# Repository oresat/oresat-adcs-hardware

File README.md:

# oresat-adcs-hardware

For more information on the OreSat project, please see <https://www.oresat.org/>!

## About this Repo

This repo contains the following projects:

* **The OreSat ADCS Card**
   * ADCS M0 microcontroller on its own OreSat Power Domain (OPD)
      * Power switch and LTC4300 that connects the M0 to:
         * BMI088 IMU (onboard the ADCS card)
         * LTC4305 2-Channel I2C Bus Multiplexer (one on each end cap via the backplane, end cards, and connectors to the end caps)
            * Two MMC5883MA magnetometers (two on each end cap, multiplexed by the LTC4305s)
      * Three STSPIN250s for the X, Y, and Z magnetorquers
   * Q1 Reaction Wheel OPD which powers the Q1 RW board
   * Q2 Reaction Wheel OPD which powers the Q2 RW board
   * Q3 Reaction Wheel OPD which powers the Q3 RW board
   * Q4 Reaction Wheel OPD which powers the Q4 RW board
* **OreSat RW boards**
   * Boards that run one of the four reaction wheels that we have.
   * Note that the "flat" version of the boards are for development

## LICENSE

Copyright the Portland State Aerospace Society, 2022.

This source describes Open Hardware that is licensed under CERN-OHL-S v2, or any later version.

You may redistribute and modify this source and make products using it under the terms of the CERN-OHL-S v2 (https://ohwr.org/cern_ohl_s_v2.txt).

This source is distributed WITHOUT ANY EXPRESS OR IMPLIED WARRANTY, INCLUDING OF MERCHANTABILITY, SATISFACTORY QUALITY AND FITNESS FOR A PARTICULAR PURPOSE. Please see the CERN-OHL-S v2 for applicable conditions.

Source location: https://github.com/oresat/

As per CERN-OHL-S v2 section 4, should You produce hardware based on this source, You must where practicable maintain the Source Location visible on the external case of the Gizmo or other products you make using this source.

# DEPRECATED - PLEASE EVENTUALLY REWRITE :)

## The OreSat Project
OreSat is an inter university collaboration to design an orbital vehicle. Once in orbit, the nanosatellite will engage in three missions. One of the missions is space testing a relatively new photovoltaic panel. The other missions require the ability to point at and maintain visual contact with a specified location. 
## Background Motivation   
In order to successfully complete these missions, OreSat will need to be able to articulate its orientation as well as its passive “drifting” spin (we’ll discuss what “passive spin” means a little later). 
Quick and reliable orientation adjustment and control will serve several purposes. It will allow the vehicle to direct its main camera, as well as giving it the ability to execute maneuvers that allow it to maintain visual and radio contact with a specific location. This makes taking photos and videos much easier, but it also allows us to have a segment of time to do large bandwidth data dumps to ground stations. This gives it the potential to do live video streaming. 
### Active Pointing
The method that was selected for active orientation on OreSat employs the use of internal spinning masses called reaction wheels. The basic principle is simple. If there is a free floating object and a section of it starts to spin, the rest of the body will react by spinning in the opposite direction. The spin rates are related, but not necessarily the same. If you’d like to look more into this, the concept is conservation of angular momentum. 
So the idea is that we have a pointing vector for Oresat (not poynting, that comes later), and an idea of the pointing vector to the location we would like to image. We simply take the difference, and then rotate the collective mass of all of the reaction wheels in the opposite direction until the satellite camera sees what we want it too.  
### Passive Spin Control
The term “passive spin” will be used to refer the net angular momentum of the nanosatellite. While the reaction wheels are active, they are able to control the direction and spin of the frame of the satellite, but only by effectively redistributing the momentum from the frame into the reaction wheel masses. The reaction wheels are incapable of altering the net angular momentum. The need for being able to modify the net momentum vector of the satellite helps alleviate the burden of two issues. The issues are thermal regulation and power generation. OreSat only has photovoltaic panels of its elongated faces. To maximize the amount of power, the desired passive spin of the satellite would put the long axis perpendicular to the sun. This maximizes the surface of exposure. There is another part to the total momentum though, and that is its magnitude. The rate of spin effects several things, but most notably it affects the temperature gradient experience by OreSat. If the satellite has no spin, then the side that the sun is hitting will heat continuously until OreSat passes behind the earth. This can cause several issues, most simply that having a hot spot would increase the likelihood of an electrical system to failing. Another issue is that the hot spot will cause different amounts of expansion in different areas of the frame, increasing the likelihood of failure. Another issue that hot spots cause is a drop in efficiency of the solar panels, making rotation partially an energy problem as well. 
Adding an intentional spin to OreSat will even out the thermal load applied to 

The attitude control system (ACS) inside oresat needs to orientate the position of the cubesat in space. This will be acheived in two ways; With brushless DC motors (BLDC) and with Magnetorquers. We are designing a PCB that controls both systems.

Find the project design contraints at,
[Project Design Constraints](https://github.com/oresat/oresat-acs-board/blob/master/Project%20Design%20Constraints.md)

ACS Level 2 Block Diagram Version 3.2

### System Hardware Overview
[Deatailed Hardware Reference Guide](https://github.com/oresat/oresat-acs-board/tree/master/Component%20File)

### EagleCAD Files:
[Link to the EagleCAD schematics and board layouts](https://github.com/oresat/oresat-acs-board/tree/master/eaglecad)

### Manufacturing Photos:
[Manufacturing photos of board layouts and CAD model of mounting strategy](https://github.com/oresat/oresat-acs-board/tree/master/Manufacturing%20photos)

### Capstone Poster:
[Link to Capstone poster in Google Drive](https://docs.google.com/presentation/d/1KBfbX376Y7nvsIXe14JdyOgP9TMmgJlgeOiYP8BOekc/edit#slide=id.p1)

### System Firmware:
[Check here for the firmware information](https://github.com/oresat/oresat-firmware/wiki/ACS-Firmware)

### Research and Tutorials / Ramp Up Documents:
Brushless DC (BLDC) motor control is a challenging form of motor control. We found numerous helpful tutorials and references.
[Link to research references and bibliography, start here for a ramp up on ACS](https://github.com/oresat/oresat-acs-board/blob/master/Ramp%20Up.md)

## Final Product:

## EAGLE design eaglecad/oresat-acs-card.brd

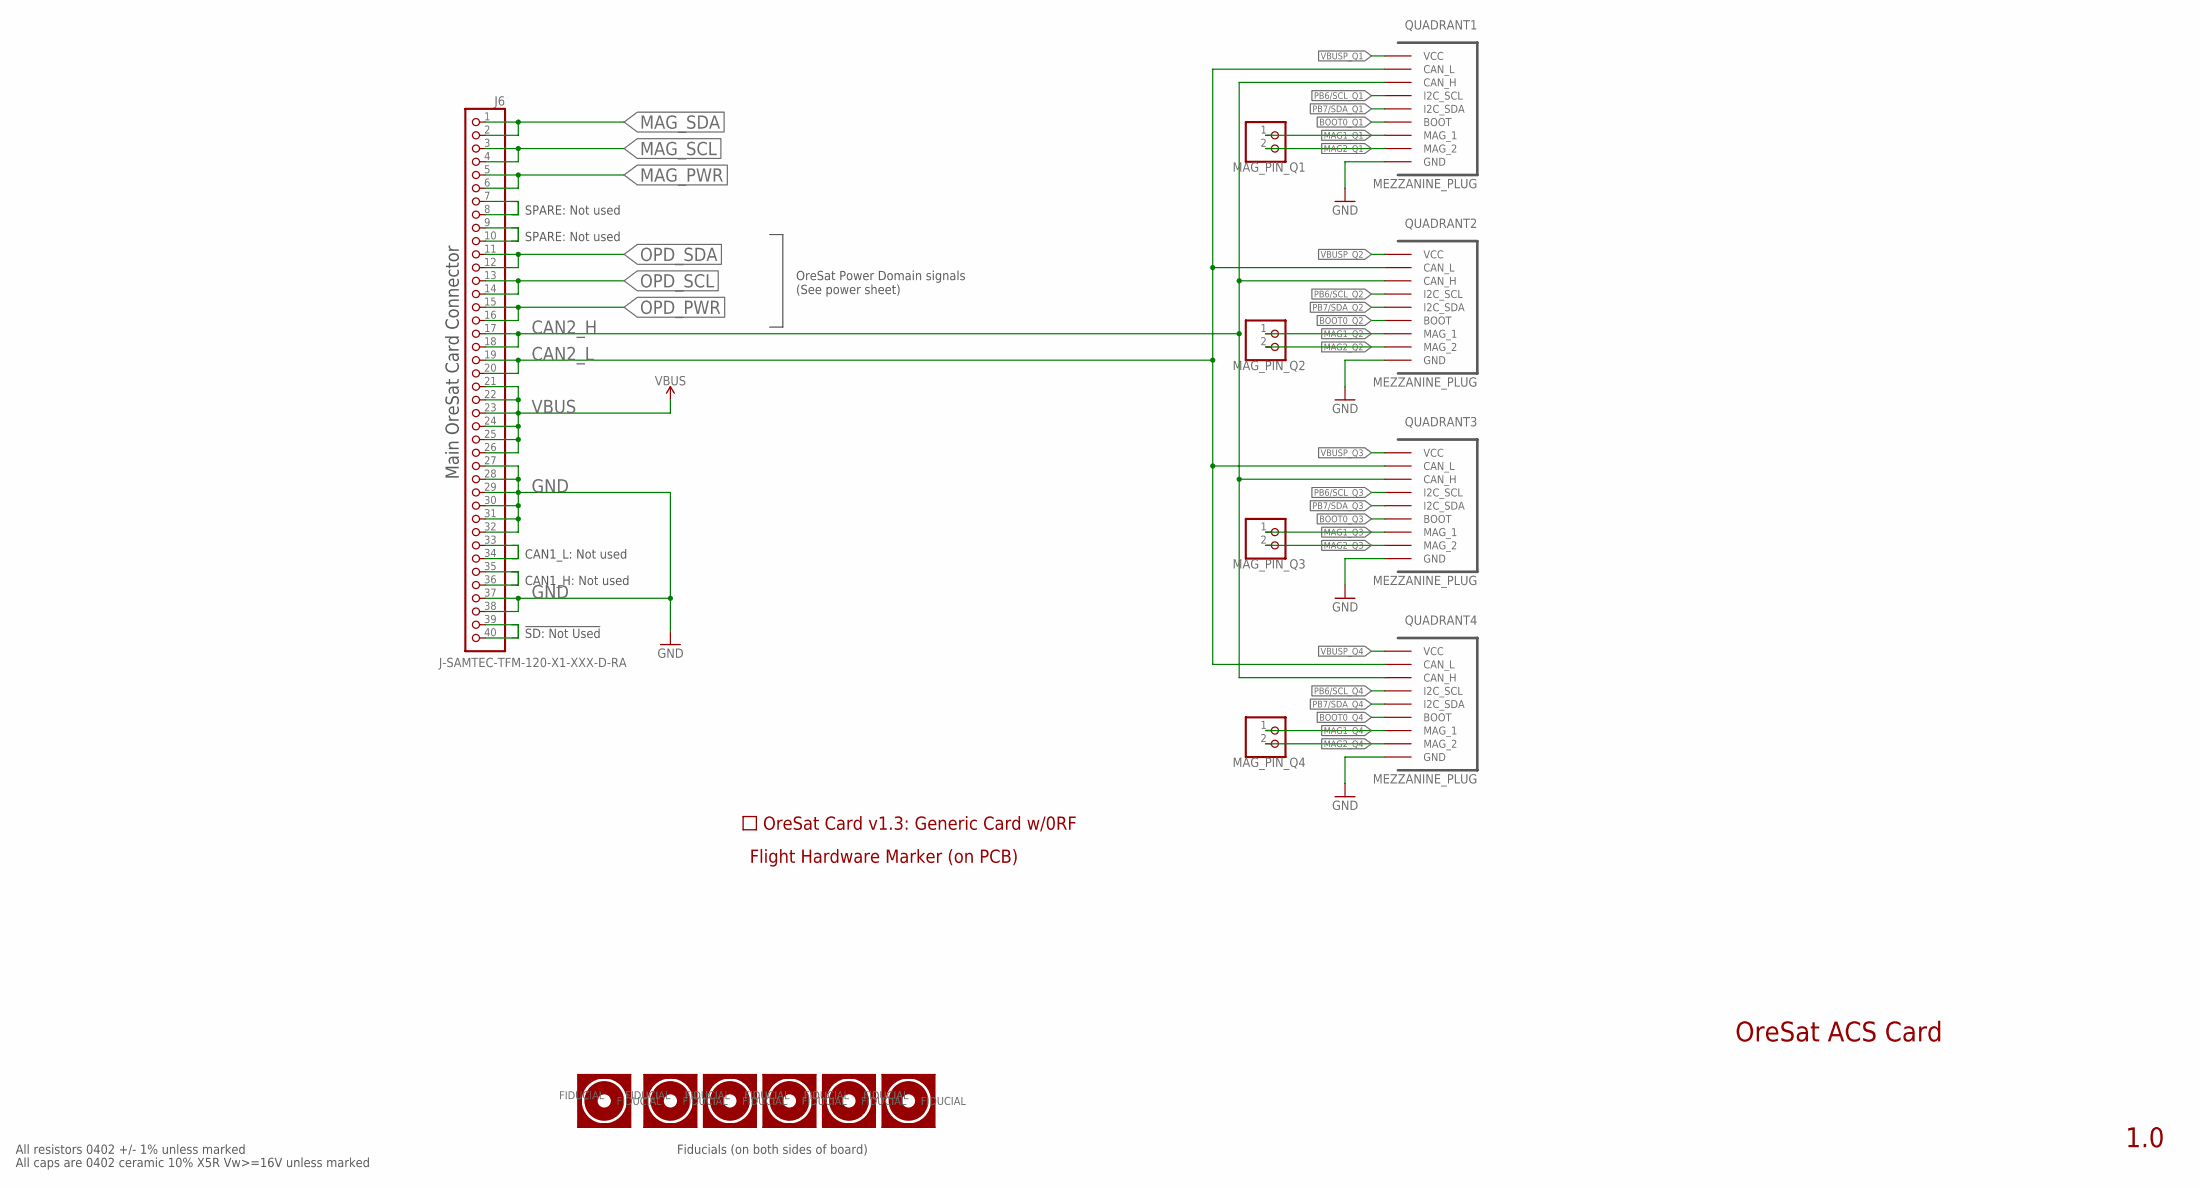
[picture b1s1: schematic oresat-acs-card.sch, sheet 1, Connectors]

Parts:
FIDUCIAL1, FIDUCIAL2, FIDUCIAL3, FIDUCIAL4, FIDUCIAL5, FIDUCIAL6: FIDUCIAL-1.0X2.0
J6: J-SAMTEC-TFM-120-X1-XXX-D-RA; MPN TFM-120-01-L-D-RA
MAG_PIN_Q1, MAG_PIN_Q2, MAG_PIN_Q3, MAG_PIN_Q4: PINHD-1X2; 1X02
PCB1: ORESAT-CARD-V1.3-GENERIC-0RF
QUADRANT1, QUADRANT2, QUADRANT3, QUADRANT4: MEZZANINE_PLUG; MPN 0555600307
U$1: FLIGHMARKERNEW; FLIGHTMARKER_NEW_BOARDS

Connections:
BOOT0_Q1: QUADRANT1.P$9 (BOOT), QUADRANT1.P$22 (BOOT); also elsewhere on the board
BOOT0_Q2: QUADRANT2.P$9 (BOOT), QUADRANT2.P$22 (BOOT); also elsewhere on the board
BOOT0_Q3: QUADRANT3.P$9 (BOOT), QUADRANT3.P$22 (BOOT); also elsewhere on the board
BOOT0_Q4: QUADRANT4.P$9 (BOOT), QUADRANT4.P$22 (BOOT); also elsewhere on the board
CAN2_H: J6.17, J6.18, QUADRANT1.P$6 (CAN_H), QUADRANT1.P$25 (CAN_H), QUADRANT2.P$6 (CAN_H), QUADRANT2.P$25 (CAN_H), QUADRANT3.P$6 (CAN_H), QUADRANT3.P$25 (CAN_H), QUADRANT4.P$6 (CAN_H), QUADRANT4.P$25 (CAN_H); also elsewhere on the board
CAN2_L: J6.19, J6.20, QUADRANT1.P$5 (CAN_L), QUADRANT1.P$26 (CAN_L), QUADRANT2.P$5 (CAN_L), QUADRANT2.P$26 (CAN_L), QUADRANT3.P$5 (CAN_L), QUADRANT3.P$26 (CAN_L), QUADRANT4.P$5 (CAN_L), QUADRANT4.P$26 (CAN_L); also elsewhere on the board
GND: J6.27, J6.28, J6.29, J6.30, J6.31, J6.32, J6.37, J6.38, QUADRANT1.P$1 (GND), QUADRANT1.P$2 (GND), QUADRANT1.P$14 (GND), QUADRANT1.P$15 (GND), QUADRANT1.P$16 (GND), QUADRANT1.P$17 (GND), QUADRANT1.P$29 (GND), QUADRANT1.P$30 (GND), QUADRANT2.P$1 (GND), QUADRANT2.P$2 (GND), QUADRANT2.P$14 (GND), QUADRANT2.P$15 (GND), QUADRANT2.P$16 (GND), QUADRANT2.P$17 (GND), QUADRANT2.P$29 (GND), QUADRANT2.P$30 (GND), QUADRANT3.P$1 (GND), QUADRANT3.P$2 (GND), QUADRANT3.P$14 (GND), QUADRANT3.P$15 (GND), QUADRANT3.P$16 (GND), QUADRANT3.P$17 (GND), QUADRANT3.P$29 (GND), QUADRANT3.P$30 (GND), QUADRANT4.P$1 (GND), QUADRANT4.P$2 (GND), QUADRANT4.P$14 (GND), QUADRANT4.P$15 (GND), QUADRANT4.P$16 (GND), QUADRANT4.P$17 (GND), QUADRANT4.P$29 (GND), QUADRANT4.P$30 (GND); also elsewhere on the board
MAG1_Q1: MAG_PIN_Q1.1, QUADRANT1.P$10 (MAG_1), QUADRANT1.P$21 (MAG_1)
MAG1_Q2: MAG_PIN_Q2.1, QUADRANT2.P$10 (MAG_1), QUADRANT2.P$21 (MAG_1)
MAG1_Q3: MAG_PIN_Q3.1, QUADRANT3.P$10 (MAG_1), QUADRANT3.P$21 (MAG_1)
MAG1_Q4: MAG_PIN_Q4.1, QUADRANT4.P$10 (MAG_1), QUADRANT4.P$21 (MAG_1)
MAG2_Q1: MAG_PIN_Q1.2, QUADRANT1.P$11 (MAG_2), QUADRANT1.P$20 (MAG_2)
MAG2_Q2: MAG_PIN_Q2.2, QUADRANT2.P$11 (MAG_2), QUADRANT2.P$20 (MAG_2)
MAG2_Q3: MAG_PIN_Q3.2, QUADRANT3.P$11 (MAG_2), QUADRANT3.P$20 (MAG_2)
MAG2_Q4: MAG_PIN_Q4.2, QUADRANT4.P$11 (MAG_2), QUADRANT4.P$20 (MAG_2)
MAG_PWR: J6.5, J6.6; also elsewhere on the board
MAG_SCL: J6.3, J6.4; also elsewhere on the board
MAG_SDA: J6.1, J6.2; also elsewhere on the board
unnamed: J6.9, J6.10
unnamed: J6.7, J6.8
unnamed: J6.39, J6.40
unnamed: J6.35, J6.36
unnamed: J6.33, J6.34
OPD_PWR: J6.15, J6.16; also elsewhere on the board
OPD_SCL: J6.13, J6.14; also elsewhere on the board
OPD_SDA: J6.11, J6.12; also elsewhere on the board
PB6/SCL_Q1: QUADRANT1.P$7 (I2C_SCL), QUADRANT1.P$24 (I2C_SCL); also elsewhere on the board
PB6/SCL_Q2: QUADRANT2.P$7 (I2C_SCL), QUADRANT2.P$24 (I2C_SCL); also elsewhere on the board
PB6/SCL_Q3: QUADRANT3.P$7 (I2C_SCL), QUADRANT3.P$24 (I2C_SCL); also elsewhere on the board
PB6/SCL_Q4: QUADRANT4.P$7 (I2C_SCL), QUADRANT4.P$24 (I2C_SCL); also elsewhere on the board
PB7/SDA_Q1: QUADRANT1.P$8 (I2C_SDA), QUADRANT1.P$23 (I2C_SDA); also elsewhere on the board
PB7/SDA_Q2: QUADRANT2.P$8 (I2C_SDA), QUADRANT2.P$23 (I2C_SDA); also elsewhere on the board
PB7/SDA_Q3: QUADRANT3.P$8 (I2C_SDA), QUADRANT3.P$23 (I2C_SDA); also elsewhere on the board
PB7/SDA_Q4: QUADRANT4.P$8 (I2C_SDA), QUADRANT4.P$23 (I2C_SDA); also elsewhere on the board
VBUS: J6.21, J6.22, J6.23, J6.24, J6.25, J6.26; also elsewhere on the board
VBUSP_Q1: QUADRANT1.P$3 (VCC), QUADRANT1.P$4 (VCC), QUADRANT1.P$12 (VCC), QUADRANT1.P$13 (VCC), QUADRANT1.P$18 (VCC), QUADRANT1.P$19 (VCC), QUADRANT1.P$27 (VCC), QUADRANT1.P$28 (VCC); also elsewhere on the board
VBUSP_Q2: QUADRANT2.P$3 (VCC), QUADRANT2.P$4 (VCC), QUADRANT2.P$12 (VCC), QUADRANT2.P$13 (VCC), QUADRANT2.P$18 (VCC), QUADRANT2.P$19 (VCC), QUADRANT2.P$27 (VCC), QUADRANT2.P$28 (VCC); also elsewhere on the board
VBUSP_Q3: QUADRANT3.P$3 (VCC), QUADRANT3.P$4 (VCC), QUADRANT3.P$12 (VCC), QUADRANT3.P$13 (VCC), QUADRANT3.P$18 (VCC), QUADRANT3.P$19 (VCC), QUADRANT3.P$27 (VCC), QUADRANT3.P$28 (VCC); also elsewhere on the board
VBUSP_Q4: QUADRANT4.P$3 (VCC), QUADRANT4.P$4 (VCC), QUADRANT4.P$12 (VCC), QUADRANT4.P$13 (VCC), QUADRANT4.P$18 (VCC), QUADRANT4.P$19 (VCC), QUADRANT4.P$27 (VCC), QUADRANT4.P$28 (VCC); also elsewhere on the board

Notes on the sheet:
OreSat ACS Card
1.0
All resistors 0402 +/- 1% unless marked
All caps are 0402 ceramic 10% X5R Vw>=16V unless marked
Main OreSat Card Connector
OreSat Power Domain signals (See power sheet)
!SD: Not Used
CAN1_H: Not used
CAN1_L: Not used
SPARE: Not used
Fiducials (on both sides of board)

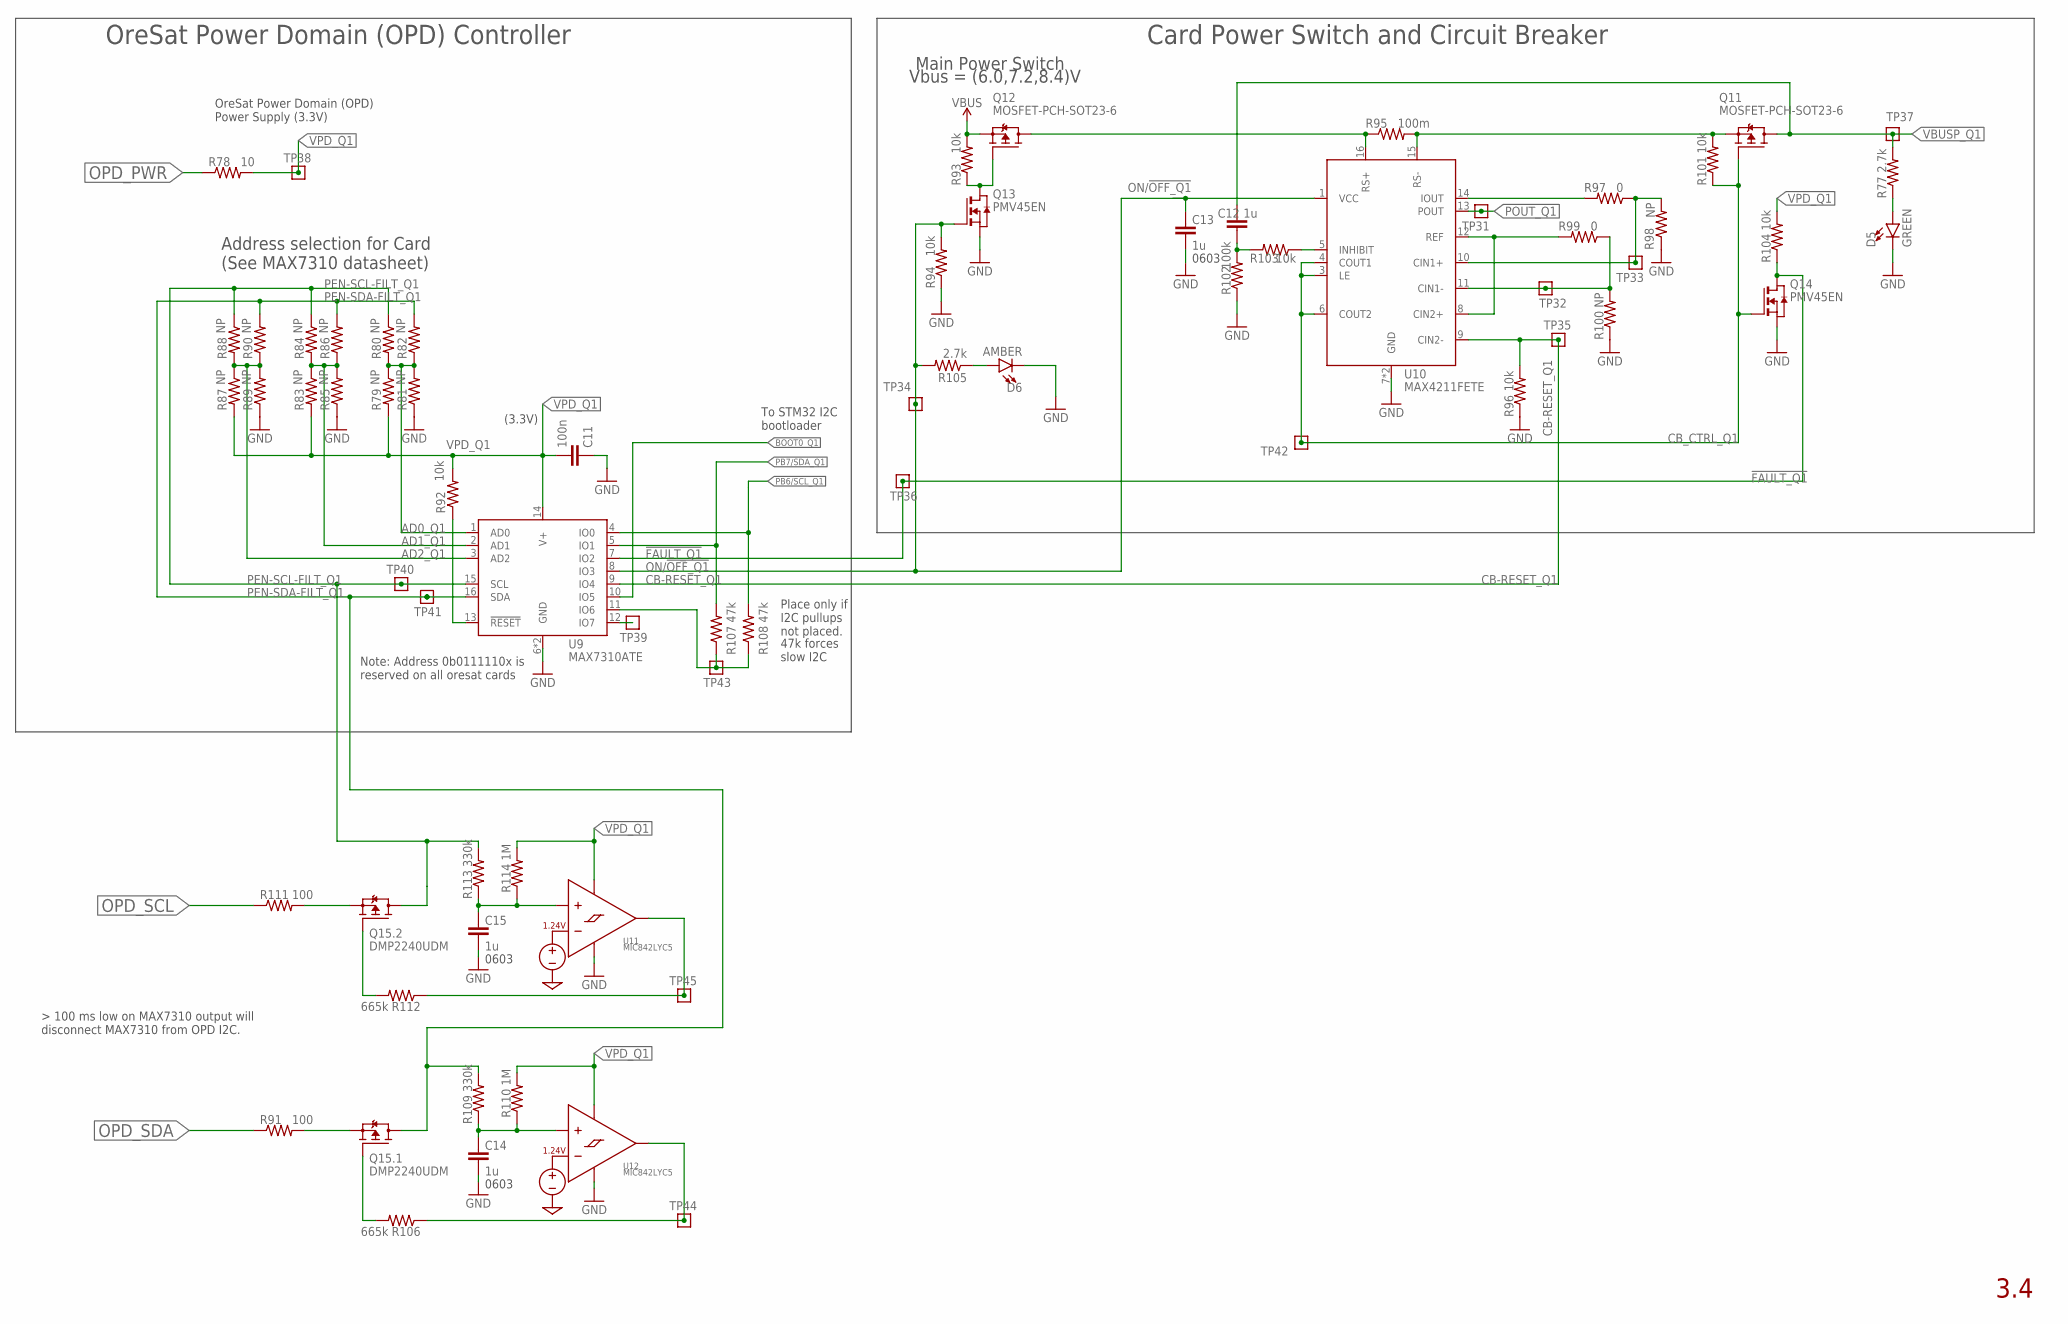
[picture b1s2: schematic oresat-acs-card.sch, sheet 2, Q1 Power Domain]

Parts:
C11: 100n; .0603-C-NOSILK; MPN CL05B104KO5NNNC
C12: 1u; .0603-C-NOSILK
C13, C14, C15: 1u; .0603-C-NOSILK; MPN CC0603KRX7R7BB105
D5: GREEN; LED-0603; MPN SML-E12M8WT86
D6: AMBER; LED-0603; MPN IN-S63AT5A
Q11, Q12: MOSFET-PCH-SOT23-6; SOT23-6; MPN DMP3050LVT-7
Q13, Q14: PMV45EN; SOT23; MPN PMV45EN2R
Q15: DMP2240UDM; SOT23-6; MPN DMP2240UDM
R77, R105: 2.7k; .0603-C-NOSILK; MPN CRGCQ0603F2K7
R78: 10; .0603-C-NOSILK; MPN RC0603FR-0710RL
R79, R80, R81, R82, R83, R84, R85, R86, R87, R88, R89, R90, R98, R100: NP; .0603-C-NOSILK; MPN RC1005F6653CS
R91, R111: 100; .0603-C-NOSILK; MPN RC0603FR-07100RL
R92, R93, R94, R96, R101, R104: 10k; .0603-C-NOSILK; MPN RC0603FR-0710KL
R95: 100m; R1206; MPN CSR1206FTR100
R97, R99: 0; .0603-C-NOSILK; MPN RC0603JR-070RL
R102: 100k; .0603-C-NOSILK; MPN RC1005F6653CS
R103: 10k; .0603-C-NOSILK; MPN RC1005F6653CS
R106, R112: 665k; .0603-C-NOSILK; MPN RC0603FR-07665KL
R107, R108: 47k; .0603-C-NOSILK; MPN RC0603FR-0747KL
R109, R113: 330k; .0603-C-NOSILK; MPN MCT06030C3303FP000
R110, R114: 1M; .0603-C-NOSILK; MPN RC0603FR-071ML
TP31, TP32, TP33, TP34, TP35, TP36, TP37, TP38, TP39, TP40, TP41, TP42, TP43, TP44, TP45: TEST-POINT-LARGE-SQUARE; 1X01
U9: MAX7310ATE; QFN65P400X400X80-17T210; MPN MAX7310ATE
U10: MAX4211FETE; QFN65P400X400X80-17T210; MPN MAX4211FETE
U11, U12: MIC842LYC5; SC70-5; MPN MIC842LYC5-TR

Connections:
!FAULT_Q1: Q14.3 (D), R104.1, TP36.1, U9.7 (IO2)
AD0_Q1: R79.1, R80.2, R81.2, R82.1, U9.1 (AD0)
AD1_Q1: R83.1, R84.2, R85.2, R86.1, U9.2 (AD1)
AD2_Q1: R87.1, R88.2, R89.2, R90.1, U9.3 (AD2)
BOOT0_Q1: U9.10 (IO5); also elsewhere on the board
CB-RESET_Q1: R96.2, TP35.1, U9.9 (IO4), U10.9 (CIN2-)
CB_CTRL_Q1: Q11.3 (G), Q14.1 (G), R101.1, TP42.1, U10.3 (LE), U10.4 (COUT1), U10.6 (COUT2)
GND: C11.1, C13.2, C14.2, C15.2, D5.C, D6.C, Q13.2 (S), Q14.2 (S), R81.1, R85.1, R89.1, R94.1, R96.1, R98.1, R100.1, R102.1, U9.6 (GND), U9.EPAD (GND), U10.7 (GND), U10.EPAD (GND), U11.2 (GND), U12.2 (GND); also elsewhere on the board
IOUT_Q1: R97.2, U10.14 (IOUT)
unnamed: TP39.1, U9.12 (IO7)
unnamed: Q15.3 (G), R112.2
unnamed: Q15.1 (G), R106.2
unnamed: D5.A, R77.1
unnamed: R92.1, U9.13 (!RESET)
unnamed: Q12.3 (G), Q13.3 (D), R93.1
unnamed: Q12.1 (D), Q12.2 (D), Q12.5 (D), Q12.6 (D), R95.1, U10.16 (RS+)
unnamed: R97.1, R98.2, TP33.1, U10.10 (CIN1+)
unnamed: R99.1, R100.2, TP32.1, U10.11 (CIN1-)
unnamed: R99.2, U10.8 (CIN2+), U10.12 (REF)
unnamed: R103.1, U10.5 (INHIBIT)
unnamed: C12.1, R102.2, R103.2
unnamed: Q11.4 (S), R95.2, R101.2, U10.15 (RS-)
unnamed: D6.A, R105.1
unnamed: Q15.5 (S), R91.2
unnamed: R106.1, TP44.1, U12.4 (OUT)
unnamed: R107.1, R108.1, TP43.1, U9.11 (IO6)
unnamed: Q15.2 (S), R111.2
unnamed: R112.1, TP45.1, U11.4 (OUT)
unnamed: C15.1, R113.1, R114.1, U11.1 (INP)
unnamed: C14.1, R109.1, R110.1, U12.1 (INP)
ON/!OFF_Q1: C13.1, Q13.1 (G), R94.2, R105.2, TP34.1, U9.8 (IO3), U10.1 (VCC)
OPD_PWR: R78.1; also elsewhere on the board
OPD_SCL: R111.1; also elsewhere on the board
OPD_SDA: R91.1; also elsewhere on the board
PB6/SCL_Q1: R108.2, U9.4 (IO0); also elsewhere on the board
PB7/SDA_Q1: R107.2, U9.5 (IO1); also elsewhere on the board
PEN-SCL-FILT_Q1: Q15.4 (D), R80.1, R84.1, R88.1, R113.2, TP40.1, U9.15 (SCL)
PEN-SDA-FILT_Q1: Q15.6 (D), R82.2, R86.2, R90.2, R109.2, TP41.1, U9.16 (SDA)
POUT_Q1: TP31.1, U10.13 (POUT)
VBUS: Q12.4 (S), R93.2; also elsewhere on the board
VBUSP_Q1: C12.2, Q11.1 (D), Q11.2 (D), Q11.5 (D), Q11.6 (D), R77.2, TP37.1; also elsewhere on the board
VPD_Q1: C11.2, R78.2, R79.2, R83.2, R87.2, R92.2, R104.2, R110.2, R114.2, TP38.1, U9.14 (V+), U11.5 (VDD), U12.5 (VDD)

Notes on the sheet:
Main Power Switch
Address selection for Card (See MAX7310 datasheet)
(3.3V)
Vbus = (6.0,7.2,8.4)V
0603
OreSat Power Domain (OPD) Power Supply (3.3V)
OreSat Power Domain (OPD) Controller
Card Power Switch and Circuit Breaker
3.4
Note: Address 0b0111110x is reserved on all oresat cards
Place only if I2C pullups not placed.
47k forces slow I2C
To STM32 I2C bootloader

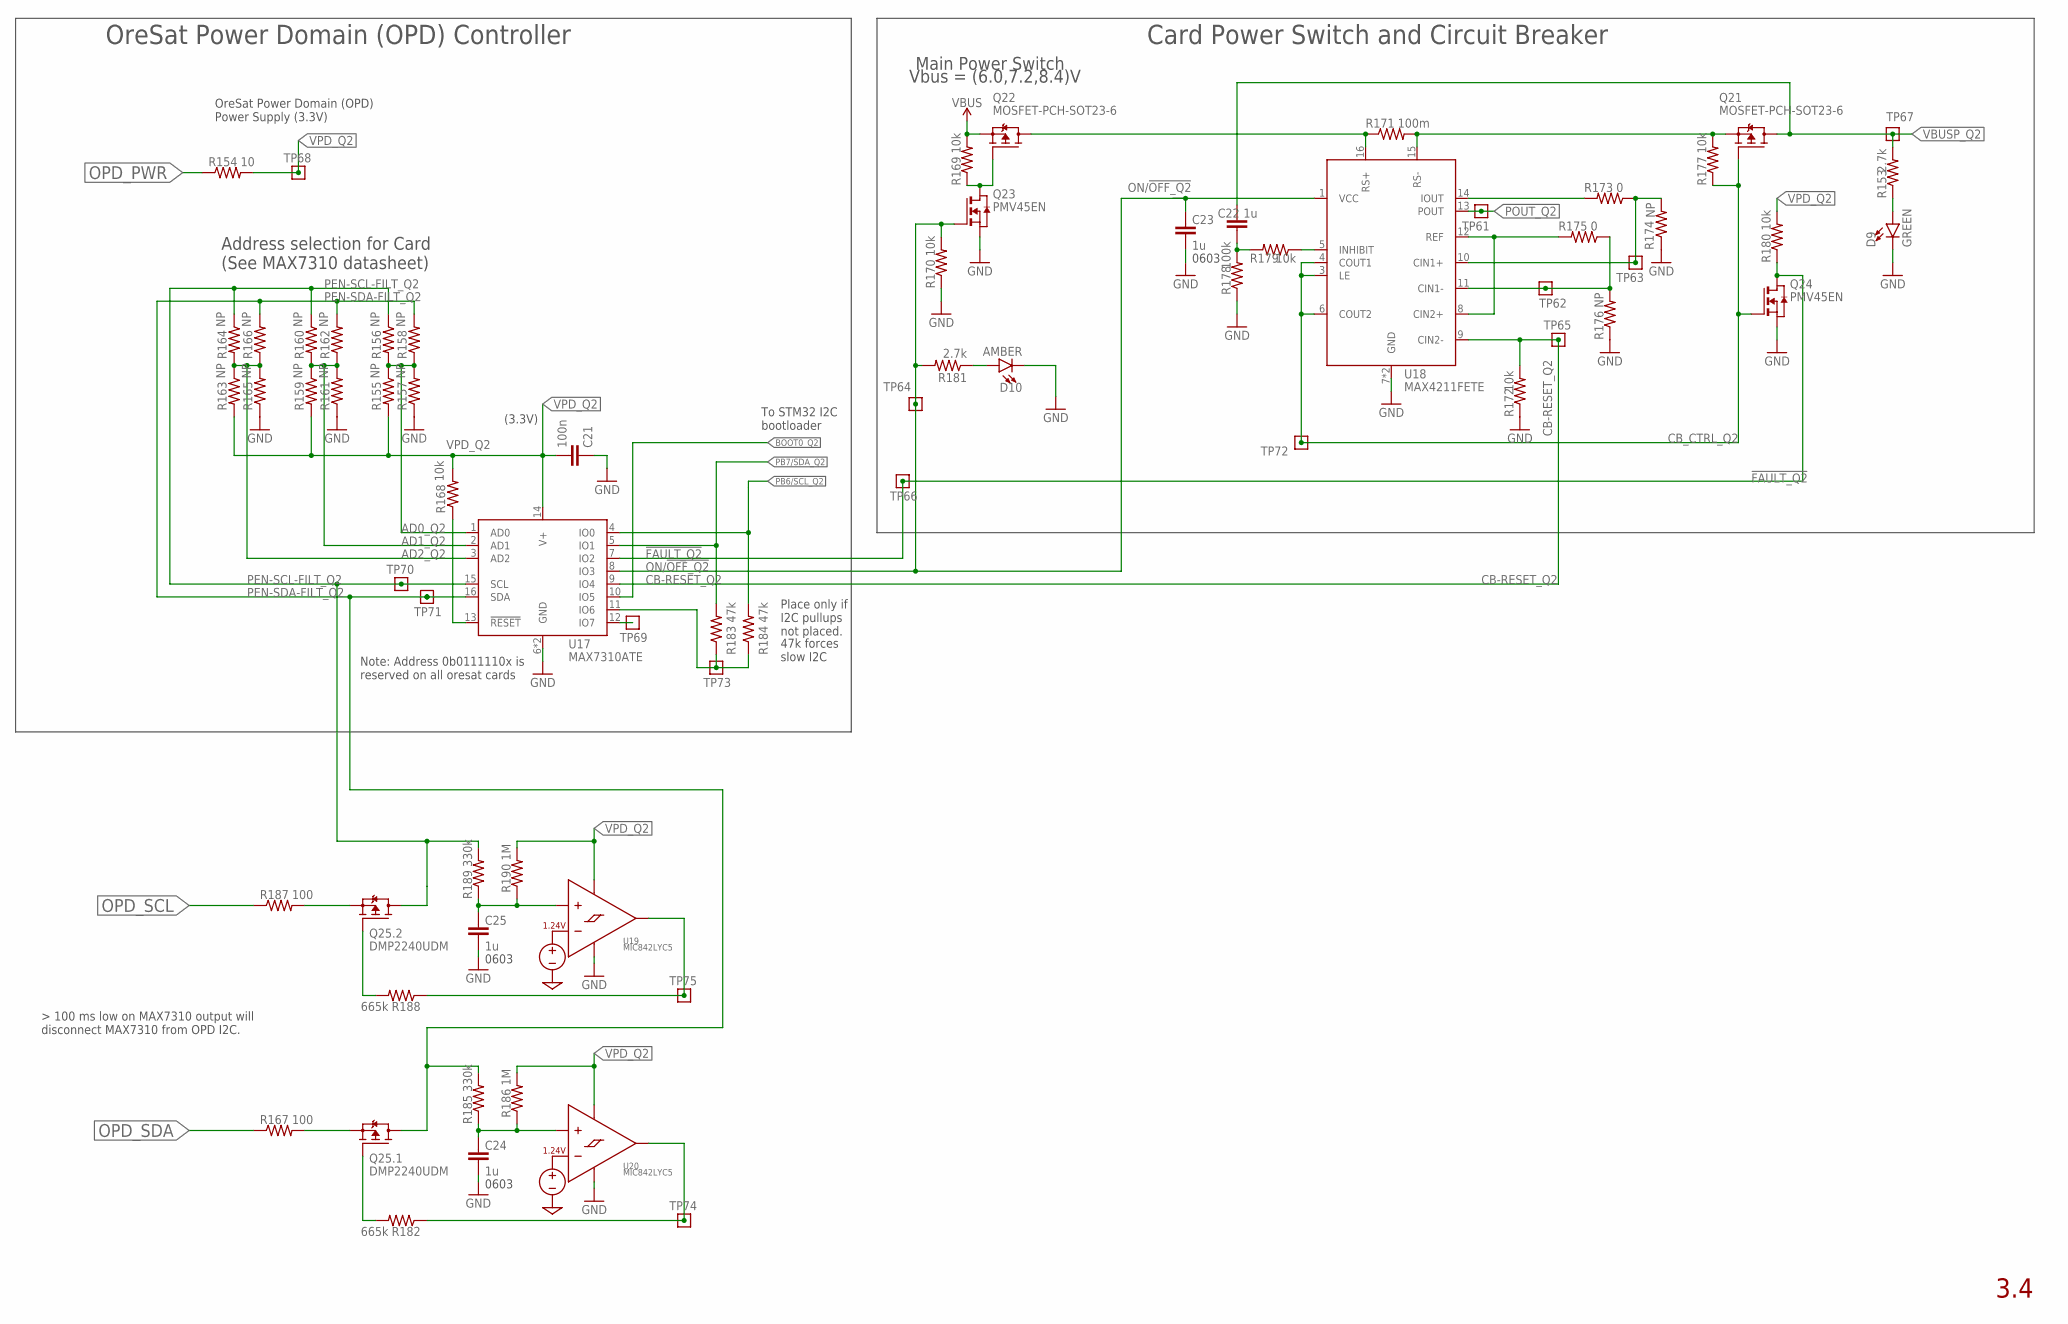
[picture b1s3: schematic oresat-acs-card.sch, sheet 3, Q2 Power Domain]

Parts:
C21: 100n; .0603-C-NOSILK; MPN CL10B104KB8NNNL
C22: 1u; .0603-C-NOSILK
C23, C24, C25: 1u; .0603-C-NOSILK; MPN CC0603KRX7R7BB105
D9: GREEN; LED-0603; MPN SML-E12M8WT86
D10: AMBER; LED-0603; MPN IN-S63AT5A
Q21, Q22: MOSFET-PCH-SOT23-6; SOT23-6; MPN DMP3050LVT-7
Q23, Q24: PMV45EN; SOT23; MPN PMV45EN2R
Q25: DMP2240UDM; SOT23-6; MPN DMP2240UDM
R153, R181: 2.7k; .0603-C-NOSILK; MPN CRGCQ0603F2K7
R154: 10; .0603-C-NOSILK; MPN RC0603FR-0710RL
R155, R156, R157, R158, R159, R160, R161, R162, R163, R164, R165, R166, R174, R176: NP; .0603-C-NOSILK; MPN RC1005F6653CS
R167, R187: 100; .0603-C-NOSILK; MPN RC0603FR-07100RL
R168, R169, R170, R172, R177, R180: 10k; .0603-C-NOSILK; MPN RC0603FR-0710KL
R171: 100m; R1206; MPN CSR1206FTR100
R173, R175: 0; .0603-C-NOSILK; MPN RC0603JR-070RL
R178: 100k; .0603-C-NOSILK; MPN RC1005F6653CS
R179: 10k; .0603-C-NOSILK; MPN RC1005F6653CS
R182, R188: 665k; .0603-C-NOSILK; MPN RC0603FR-07665KL
R183, R184: 47k; .0603-C-NOSILK; MPN RC0603FR-0747KL
R185, R189: 330k; .0603-C-NOSILK; MPN MCT06030C3303FP000
R186, R190: 1M; .0603-C-NOSILK; MPN RC0603FR-071ML
TP61, TP62, TP63, TP64, TP65, TP66, TP67, TP68, TP69, TP70, TP71, TP72, TP73, TP74, TP75: TEST-POINT-LARGE-SQUARE; 1X01
U17: MAX7310ATE; QFN65P400X400X80-17T210; MPN MAX7310ATE
U18: MAX4211FETE; QFN65P400X400X80-17T210; MPN MAX4211FETE
U19, U20: MIC842LYC5; SC70-5; MPN MIC842LYC5-TR

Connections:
!FAULT_Q2: Q24.3 (D), R180.1, TP66.1, U17.7 (IO2)
AD0_Q2: R155.1, R156.2, R157.2, R158.1, U17.1 (AD0)
AD1_Q2: R159.1, R160.2, R161.2, R162.1, U17.2 (AD1)
AD2_Q2: R163.1, R164.2, R165.2, R166.1, U17.3 (AD2)
BOOT0_Q2: U17.10 (IO5); also elsewhere on the board
CB-RESET_Q2: R172.2, TP65.1, U17.9 (IO4), U18.9 (CIN2-)
CB_CTRL_Q2: Q21.3 (G), Q24.1 (G), R177.1, TP72.1, U18.3 (LE), U18.4 (COUT1), U18.6 (COUT2)
GND: C21.1, C23.2, C24.2, C25.2, D9.C, D10.C, Q23.2 (S), Q24.2 (S), R157.1, R161.1, R165.1, R170.1, R172.1, R174.1, R176.1, R178.1, U17.6 (GND), U17.EPAD (GND), U18.7 (GND), U18.EPAD (GND), U19.2 (GND), U20.2 (GND); also elsewhere on the board
IOUT_Q2: R173.2, U18.14 (IOUT)
unnamed: TP69.1, U17.12 (IO7)
unnamed: Q25.3 (G), R188.2
unnamed: Q25.1 (G), R182.2
unnamed: D9.A, R153.1
unnamed: R168.1, U17.13 (!RESET)
unnamed: Q22.3 (G), Q23.3 (D), R169.1
unnamed: Q22.1 (D), Q22.2 (D), Q22.5 (D), Q22.6 (D), R171.1, U18.16 (RS+)
unnamed: R173.1, R174.2, TP63.1, U18.10 (CIN1+)
unnamed: R175.1, R176.2, TP62.1, U18.11 (CIN1-)
unnamed: R175.2, U18.8 (CIN2+), U18.12 (REF)
unnamed: R179.1, U18.5 (INHIBIT)
unnamed: C22.1, R178.2, R179.2
unnamed: Q21.4 (S), R171.2, R177.2, U18.15 (RS-)
unnamed: D10.A, R181.1
unnamed: Q25.5 (S), R167.2
unnamed: R182.1, TP74.1, U20.4 (OUT)
unnamed: R183.1, R184.1, TP73.1, U17.11 (IO6)
unnamed: Q25.2 (S), R187.2
unnamed: R188.1, TP75.1, U19.4 (OUT)
unnamed: C25.1, R189.1, R190.1, U19.1 (INP)
unnamed: C24.1, R185.1, R186.1, U20.1 (INP)
ON/!OFF_Q2: C23.1, Q23.1 (G), R170.2, R181.2, TP64.1, U17.8 (IO3), U18.1 (VCC)
OPD_PWR: R154.1; also elsewhere on the board
OPD_SCL: R187.1; also elsewhere on the board
OPD_SDA: R167.1; also elsewhere on the board
PB6/SCL_Q2: R184.2, U17.4 (IO0); also elsewhere on the board
PB7/SDA_Q2: R183.2, U17.5 (IO1); also elsewhere on the board
PEN-SCL-FILT_Q2: Q25.4 (D), R156.1, R160.1, R164.1, R189.2, TP70.1, U17.15 (SCL)
PEN-SDA-FILT_Q2: Q25.6 (D), R158.2, R162.2, R166.2, R185.2, TP71.1, U17.16 (SDA)
POUT_Q2: TP61.1, U18.13 (POUT)
VBUS: Q22.4 (S), R169.2; also elsewhere on the board
VBUSP_Q2: C22.2, Q21.1 (D), Q21.2 (D), Q21.5 (D), Q21.6 (D), R153.2, TP67.1; also elsewhere on the board
VPD_Q2: C21.2, R154.2, R155.2, R159.2, R163.2, R168.2, R180.2, R186.2, R190.2, TP68.1, U17.14 (V+), U19.5 (VDD), U20.5 (VDD)

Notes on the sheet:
Main Power Switch
Address selection for Card (See MAX7310 datasheet)
(3.3V)
Vbus = (6.0,7.2,8.4)V
0603
OreSat Power Domain (OPD) Power Supply (3.3V)
OreSat Power Domain (OPD) Controller
Card Power Switch and Circuit Breaker
3.4
Note: Address 0b0111110x is reserved on all oresat cards
Place only if I2C pullups not placed.
47k forces slow I2C
To STM32 I2C bootloader

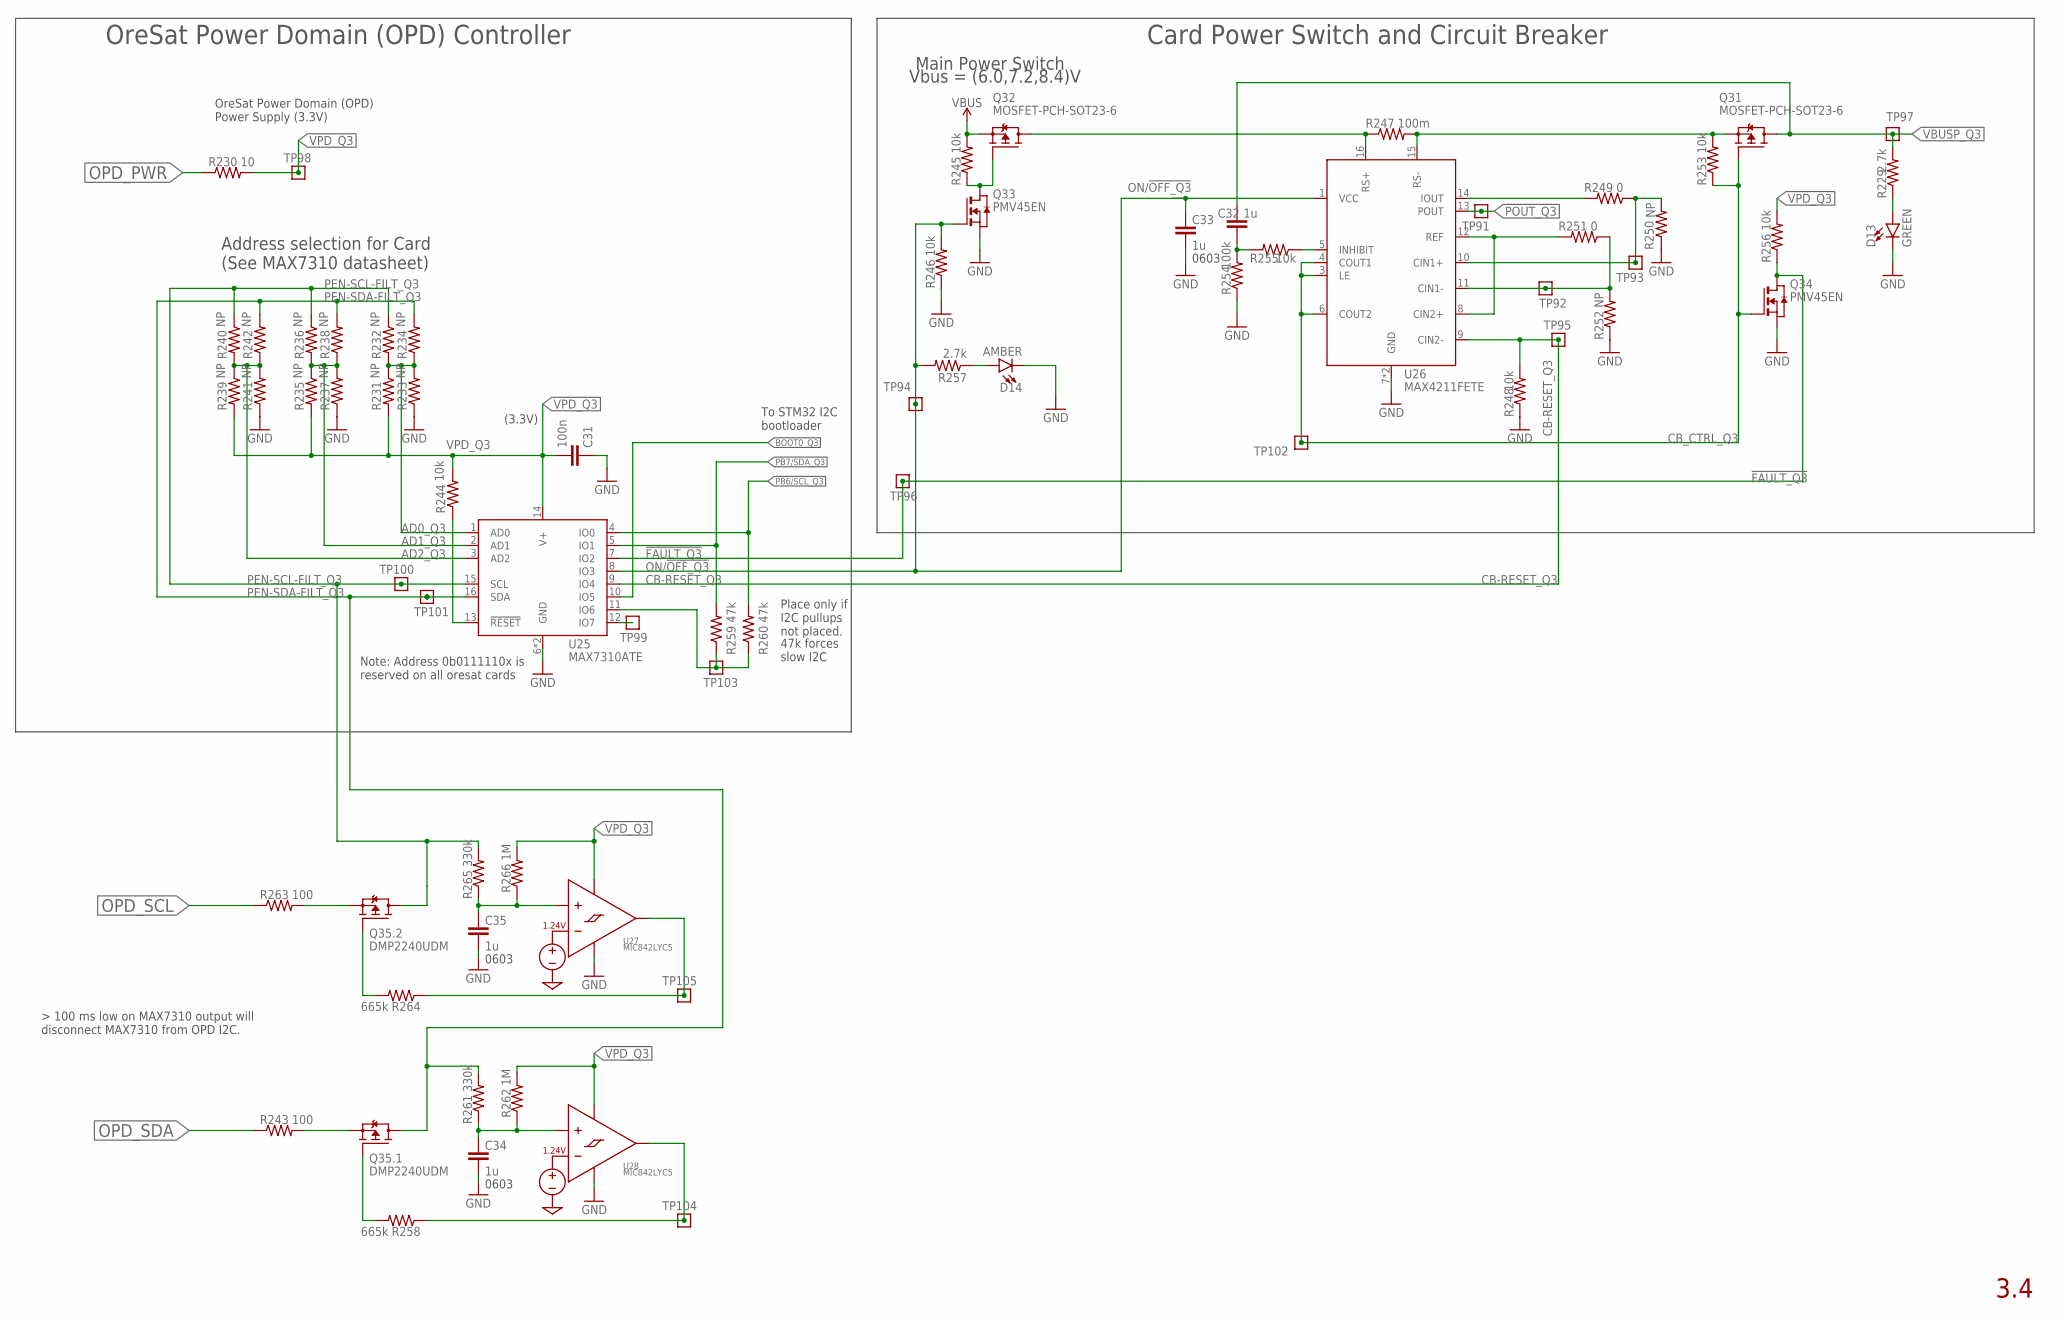
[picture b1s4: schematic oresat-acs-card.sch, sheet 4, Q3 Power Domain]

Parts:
C31: 100n; .0603-C-NOSILK; MPN CL10B104KB8NNNL
C32: 1u; .0603-C-NOSILK
C33, C34, C35: 1u; .0603-C-NOSILK; MPN CC0603KRX7R7BB105
D13: GREEN; LED-0603; MPN SML-E12M8WT86
D14: AMBER; LED-0603; MPN IN-S63AT5A
Q31, Q32: MOSFET-PCH-SOT23-6; SOT23-6; MPN DMP3050LVT-7
Q33, Q34: PMV45EN; SOT23; MPN PMV45EN2R
Q35: DMP2240UDM; SOT23-6; MPN DMP2240UDM
R229, R257: 2.7k; .0603-C-NOSILK; MPN CRGCQ0603F2K7
R230: 10; .0603-C-NOSILK; MPN RC0603FR-0710RL
R231, R232, R233, R234, R235, R236, R237, R238, R239, R240, R241, R242, R250, R252: NP; .0603-C-NOSILK; MPN RC1005F6653CS
R243, R263: 100; .0603-C-NOSILK; MPN RC0603FR-07100RL
R244, R245, R246, R248, R253, R256: 10k; .0603-C-NOSILK; MPN RC0603FR-0710KL
R247: 100m; R1206; MPN CSR1206FTR100
R249, R251: 0; .0603-C-NOSILK; MPN RC0603JR-070RL
R254: 100k; .0603-C-NOSILK; MPN RC1005F6653CS
R255: 10k; .0603-C-NOSILK; MPN RC1005F6653CS
R258, R264: 665k; .0603-C-NOSILK; MPN RC0603FR-07665KL
R259, R260: 47k; .0603-C-NOSILK; MPN RC0603FR-0747KL
R261, R265: 330k; .0603-C-NOSILK; MPN MCT06030C3303FP000
R262, R266: 1M; .0603-C-NOSILK; MPN RC0603FR-071ML
TP91, TP92, TP93, TP94, TP95, TP96, TP97, TP98, TP99, TP100, TP101, TP102, TP103, TP104, TP105: TEST-POINT-LARGE-SQUARE; 1X01
U25: MAX7310ATE; QFN65P400X400X80-17T210; MPN MAX7310ATE
U26: MAX4211FETE; QFN65P400X400X80-17T210; MPN MAX4211FETE
U27, U28: MIC842LYC5; SC70-5; MPN MIC842LYC5-TR

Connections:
!FAULT_Q3: Q34.3 (D), R256.1, TP96.1, U25.7 (IO2)
AD0_Q3: R231.1, R232.2, R233.2, R234.1, U25.1 (AD0)
AD1_Q3: R235.1, R236.2, R237.2, R238.1, U25.2 (AD1)
AD2_Q3: R239.1, R240.2, R241.2, R242.1, U25.3 (AD2)
BOOT0_Q3: U25.10 (IO5); also elsewhere on the board
CB-RESET_Q3: R248.2, TP95.1, U25.9 (IO4), U26.9 (CIN2-)
CB_CTRL_Q3: Q31.3 (G), Q34.1 (G), R253.1, TP102.1, U26.3 (LE), U26.4 (COUT1), U26.6 (COUT2)
GND: C31.1, C33.2, C34.2, C35.2, D13.C, D14.C, Q33.2 (S), Q34.2 (S), R233.1, R237.1, R241.1, R246.1, R248.1, R250.1, R252.1, R254.1, U25.6 (GND), U25.EPAD (GND), U26.7 (GND), U26.EPAD (GND), U27.2 (GND), U28.2 (GND); also elsewhere on the board
IOUT_Q_3: R249.2, U26.14 (IOUT)
unnamed: TP99.1, U25.12 (IO7)
unnamed: Q35.1 (G), R258.2
unnamed: Q35.3 (G), R264.2
unnamed: D13.A, R229.1
unnamed: R244.1, U25.13 (!RESET)
unnamed: Q32.3 (G), Q33.3 (D), R245.1
unnamed: Q32.1 (D), Q32.2 (D), Q32.5 (D), Q32.6 (D), R247.1, U26.16 (RS+)
unnamed: R249.1, R250.2, TP93.1, U26.10 (CIN1+)
unnamed: R251.1, R252.2, TP92.1, U26.11 (CIN1-)
unnamed: R251.2, U26.8 (CIN2+), U26.12 (REF)
unnamed: R255.1, U26.5 (INHIBIT)
unnamed: C32.1, R254.2, R255.2
unnamed: Q31.4 (S), R247.2, R253.2, U26.15 (RS-)
unnamed: D14.A, R257.1
unnamed: Q35.5 (S), R243.2
unnamed: R258.1, TP104.1, U28.4 (OUT)
unnamed: R259.1, R260.1, TP103.1, U25.11 (IO6)
unnamed: Q35.2 (S), R263.2
unnamed: R264.1, TP105.1, U27.4 (OUT)
unnamed: C35.1, R265.1, R266.1, U27.1 (INP)
unnamed: C34.1, R261.1, R262.1, U28.1 (INP)
ON/!OFF_Q3: C33.1, Q33.1 (G), R246.2, R257.2, TP94.1, U25.8 (IO3), U26.1 (VCC)
OPD_PWR: R230.1; also elsewhere on the board
OPD_SCL: R263.1; also elsewhere on the board
OPD_SDA: R243.1; also elsewhere on the board
PB6/SCL_Q3: R260.2, U25.4 (IO0); also elsewhere on the board
PB7/SDA_Q3: R259.2, U25.5 (IO1); also elsewhere on the board
PEN-SCL-FILT_Q3: Q35.4 (D), R232.1, R236.1, R240.1, R265.2, TP100.1, U25.15 (SCL)
PEN-SDA-FILT_Q3: Q35.6 (D), R234.2, R238.2, R242.2, R261.2, TP101.1, U25.16 (SDA)
POUT_Q3: TP91.1, U26.13 (POUT)
VBUS: Q32.4 (S), R245.2; also elsewhere on the board
VBUSP_Q3: C32.2, Q31.1 (D), Q31.2 (D), Q31.5 (D), Q31.6 (D), R229.2, TP97.1; also elsewhere on the board
VPD_Q3: C31.2, R230.2, R231.2, R235.2, R239.2, R244.2, R256.2, R262.2, R266.2, TP98.1, U25.14 (V+), U27.5 (VDD), U28.5 (VDD)

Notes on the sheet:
Main Power Switch
Address selection for Card (See MAX7310 datasheet)
(3.3V)
Vbus = (6.0,7.2,8.4)V
0603
OreSat Power Domain (OPD) Power Supply (3.3V)
OreSat Power Domain (OPD) Controller
Card Power Switch and Circuit Breaker
3.4
Note: Address 0b0111110x is reserved on all oresat cards
Place only if I2C pullups not placed.
47k forces slow I2C
To STM32 I2C bootloader

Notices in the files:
parts and their libraries:
SparkFun-Connectors: Licensing: Creative Commons ShareAlike 4.0 International - https://creativecommons.org/licenses/by-sa/4.0
